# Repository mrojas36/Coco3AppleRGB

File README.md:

# Coco3AppleRGB

This card will interface the **Color Computer 3 RGB port** to an **AppleColor RGB Monitor (model A2M6014)**.  It was created and shared with the CoCo community.  The design is provided here for whatever purpose you would like: make for yourself, build, sell, or modify.

## Overview

The card was designed from an schematic from 1996 by Tomi Engdahl.  The circuit was modified to work with the AppleColor RGB Monitor. Here is the original schematic:

I bread boarded this circuit and made modifications (shown in pencil) to get it to work with the Apple Monitor. 

With a bit of fiddling, I was able to achieve a display:

The key to getting this to work was recognizing that the Apple Monitor needs a *composite* sync (CSYNC) in order to display.  The CoCo3 has separate horizontal and vertical sync signals.  This circuit will take those signals, flip them, and then interface them into a composite signal (show on the oscilloscope).  Here is the resulting schematic:

## Design

The project was built in **Kicad** and has all the project files included.  You can get a copy of Kicad from https://www.kicad.org.

Kicad was also used to layout of the PCB, show here:

The bill of material is straightforward and only contains easy to find parts.  At the time of writing the total board cost is under $7 USD.

The finished board:

## Case

This project also contains a 3D printable case design.  The case is in two parts: Top and Bottom.  No screws are needed as the bottom slides into the top part for a snug fit.

The case was designed using **DesignSpark Mechanical**.  This is a free design tool.  You can download the tool from https://www.rs-online.com/designspark/mechanical-software.  The design files are included in the Case folder.

Here are some photos of the finished case:

## Additional Parts

The adapter works very well and 80 column text is very legible. To complete the set you will need a **5VDC Power Adaptor with a 5.5mm x 2.5mm plug, center positive**.  You will also need a **10 pin ribbon cable** to connect to the underside of the CoCo3.

## Complete - Enjoy!

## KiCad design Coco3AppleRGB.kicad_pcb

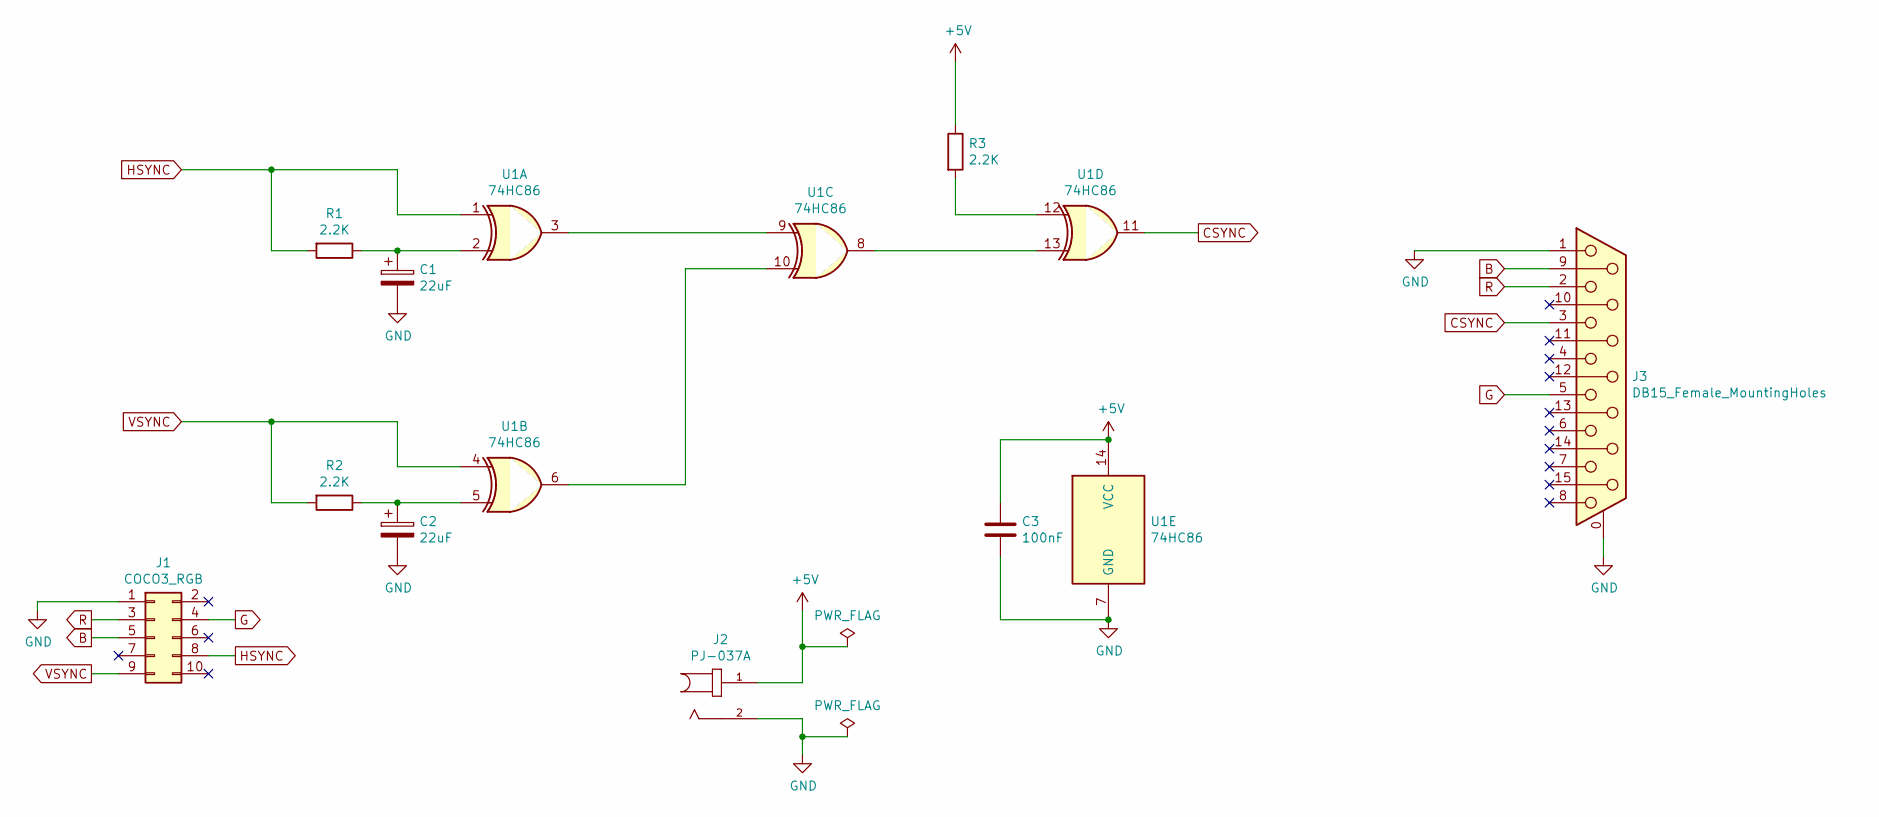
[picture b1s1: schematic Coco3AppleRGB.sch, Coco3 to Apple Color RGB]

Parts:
C1, C2: 22uF; C_1210_3225Metric_Pad1.33x2.70mm_HandSolder
C3: 100nF; C_0805_2012Metric_Pad1.18x1.45mm_HandSolder
J1: COCO3_RGB; IDC-Header_2x05_P2.54mm_Vertical
J2: PJ-037A; CUI_PJ-037A
J3: DB15_Female_MountingHoles; DSUB-15_Female_Horizontal_P2.77x2.84mm_EdgePinOffset9.90mm_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
R1, R2, R3: 2.2K; R_1206_3216Metric_Pad1.30x1.75mm_HandSolder
U1: 74HC86; TSSOP-14_4.4x5mm_P0.65mm

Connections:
+5V: C3.1, J2.1, R3.1, U1.14 (VCC)
B: J1.5, J3.9
CSYNC: J3.3, U1.11
G: J1.4, J3.5
GND: C1.2, C2.2, C3.2, J1.1, J2.2, J3.0 (PAD), J3.1, U1.7 (GND)
HSYNC: J1.8, R1.2, U1.1
unnamed: C1.1, R1.1, U1.2
unnamed: C2.1, R2.1, U1.5
unnamed: R3.2, U1.12
unnamed: U1.3, U1.9
unnamed: U1.6, U1.10
unnamed: U1.8, U1.13
R: J1.3, J3.2
VSYNC: J1.9, R2.2, U1.4

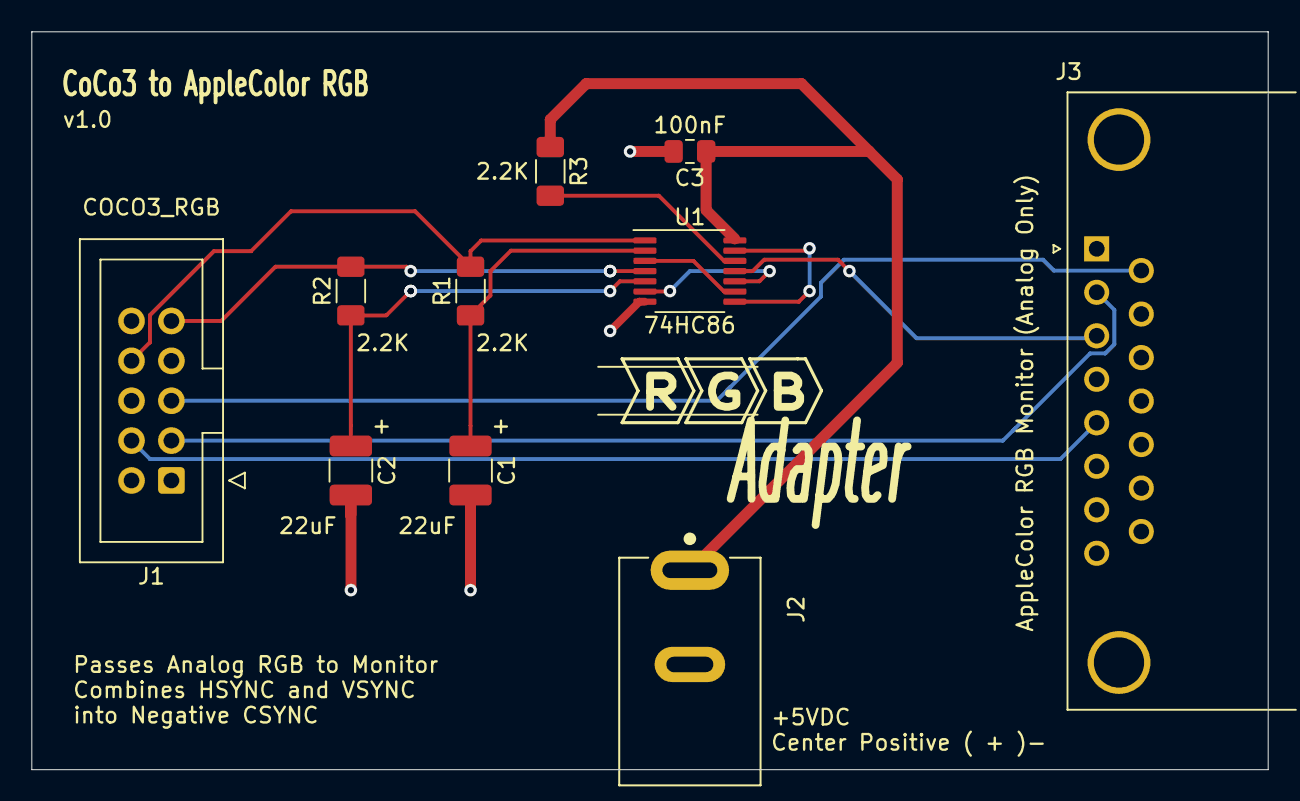
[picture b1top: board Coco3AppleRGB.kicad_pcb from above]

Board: 2 copper layers, 78.7 x 47.0 mm, 10 parts (0 on the bottom side), 14 nets.

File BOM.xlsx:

Id | Designator | Package | Quantity | Designation | Supplier and ref | Unit Price | Extended
1 | J2 | CUI_PJ-037A | 1 | +5VDC Power | Digikey | 0.50800000000000001 | 0.50800000000000001
2 | R3,R2,R1 | R_1206_3216Metric_Pad1.30x1.75mm_HandSolder | 3 | 2.2K | Digikey | 2.8000000000000001E-2 | 8.4000000000000005E-2
3 | U1 | TSSOP-14_4.4x5mm_P0.65mm | 1 | 74HC86 | Digikey | 0.35899999999999999 | 0.35899999999999999
4 | J3 | DSUB-15_Female_Horizontal_P2.77x2.84mm_EdgePinOffset9.90mm_Housed_MountingHoles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 | 1 | DB15_Female_MountingHoles | Digikey | 0.97199999999999998 | 0.97199999999999998
5 | J1 | IDC-Header_2x05_P2.54mm_Vertical | 1 | COCO3_RGB | Digikey | 0.36 | 0.36
6 | C3 | C_0805_2012Metric_Pad1.18x1.45mm_HandSolder | 1 | 100nF | Digikey | 0.16700000000000001 | 0.16700000000000001
7 | C2,C1 | CP_EIA-7132-20_AVX-U_Pad2.72x3.50mm_HandSolder | 2 | 22uF | Digikey | 0.309 | 0.61799999999999999
 |  | unit price on order of 10 units |  |  | Total parts (each) |  | 3.0679999999999996
 |  |  |  |  | PCB (each) |  | 3.9
 |  |  |  |  | Total Kit |  | 6.968

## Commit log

2021-09-05 More Photos
2021-09-09 New Case Design
2021-09-10 Adjusted hole size for screws
